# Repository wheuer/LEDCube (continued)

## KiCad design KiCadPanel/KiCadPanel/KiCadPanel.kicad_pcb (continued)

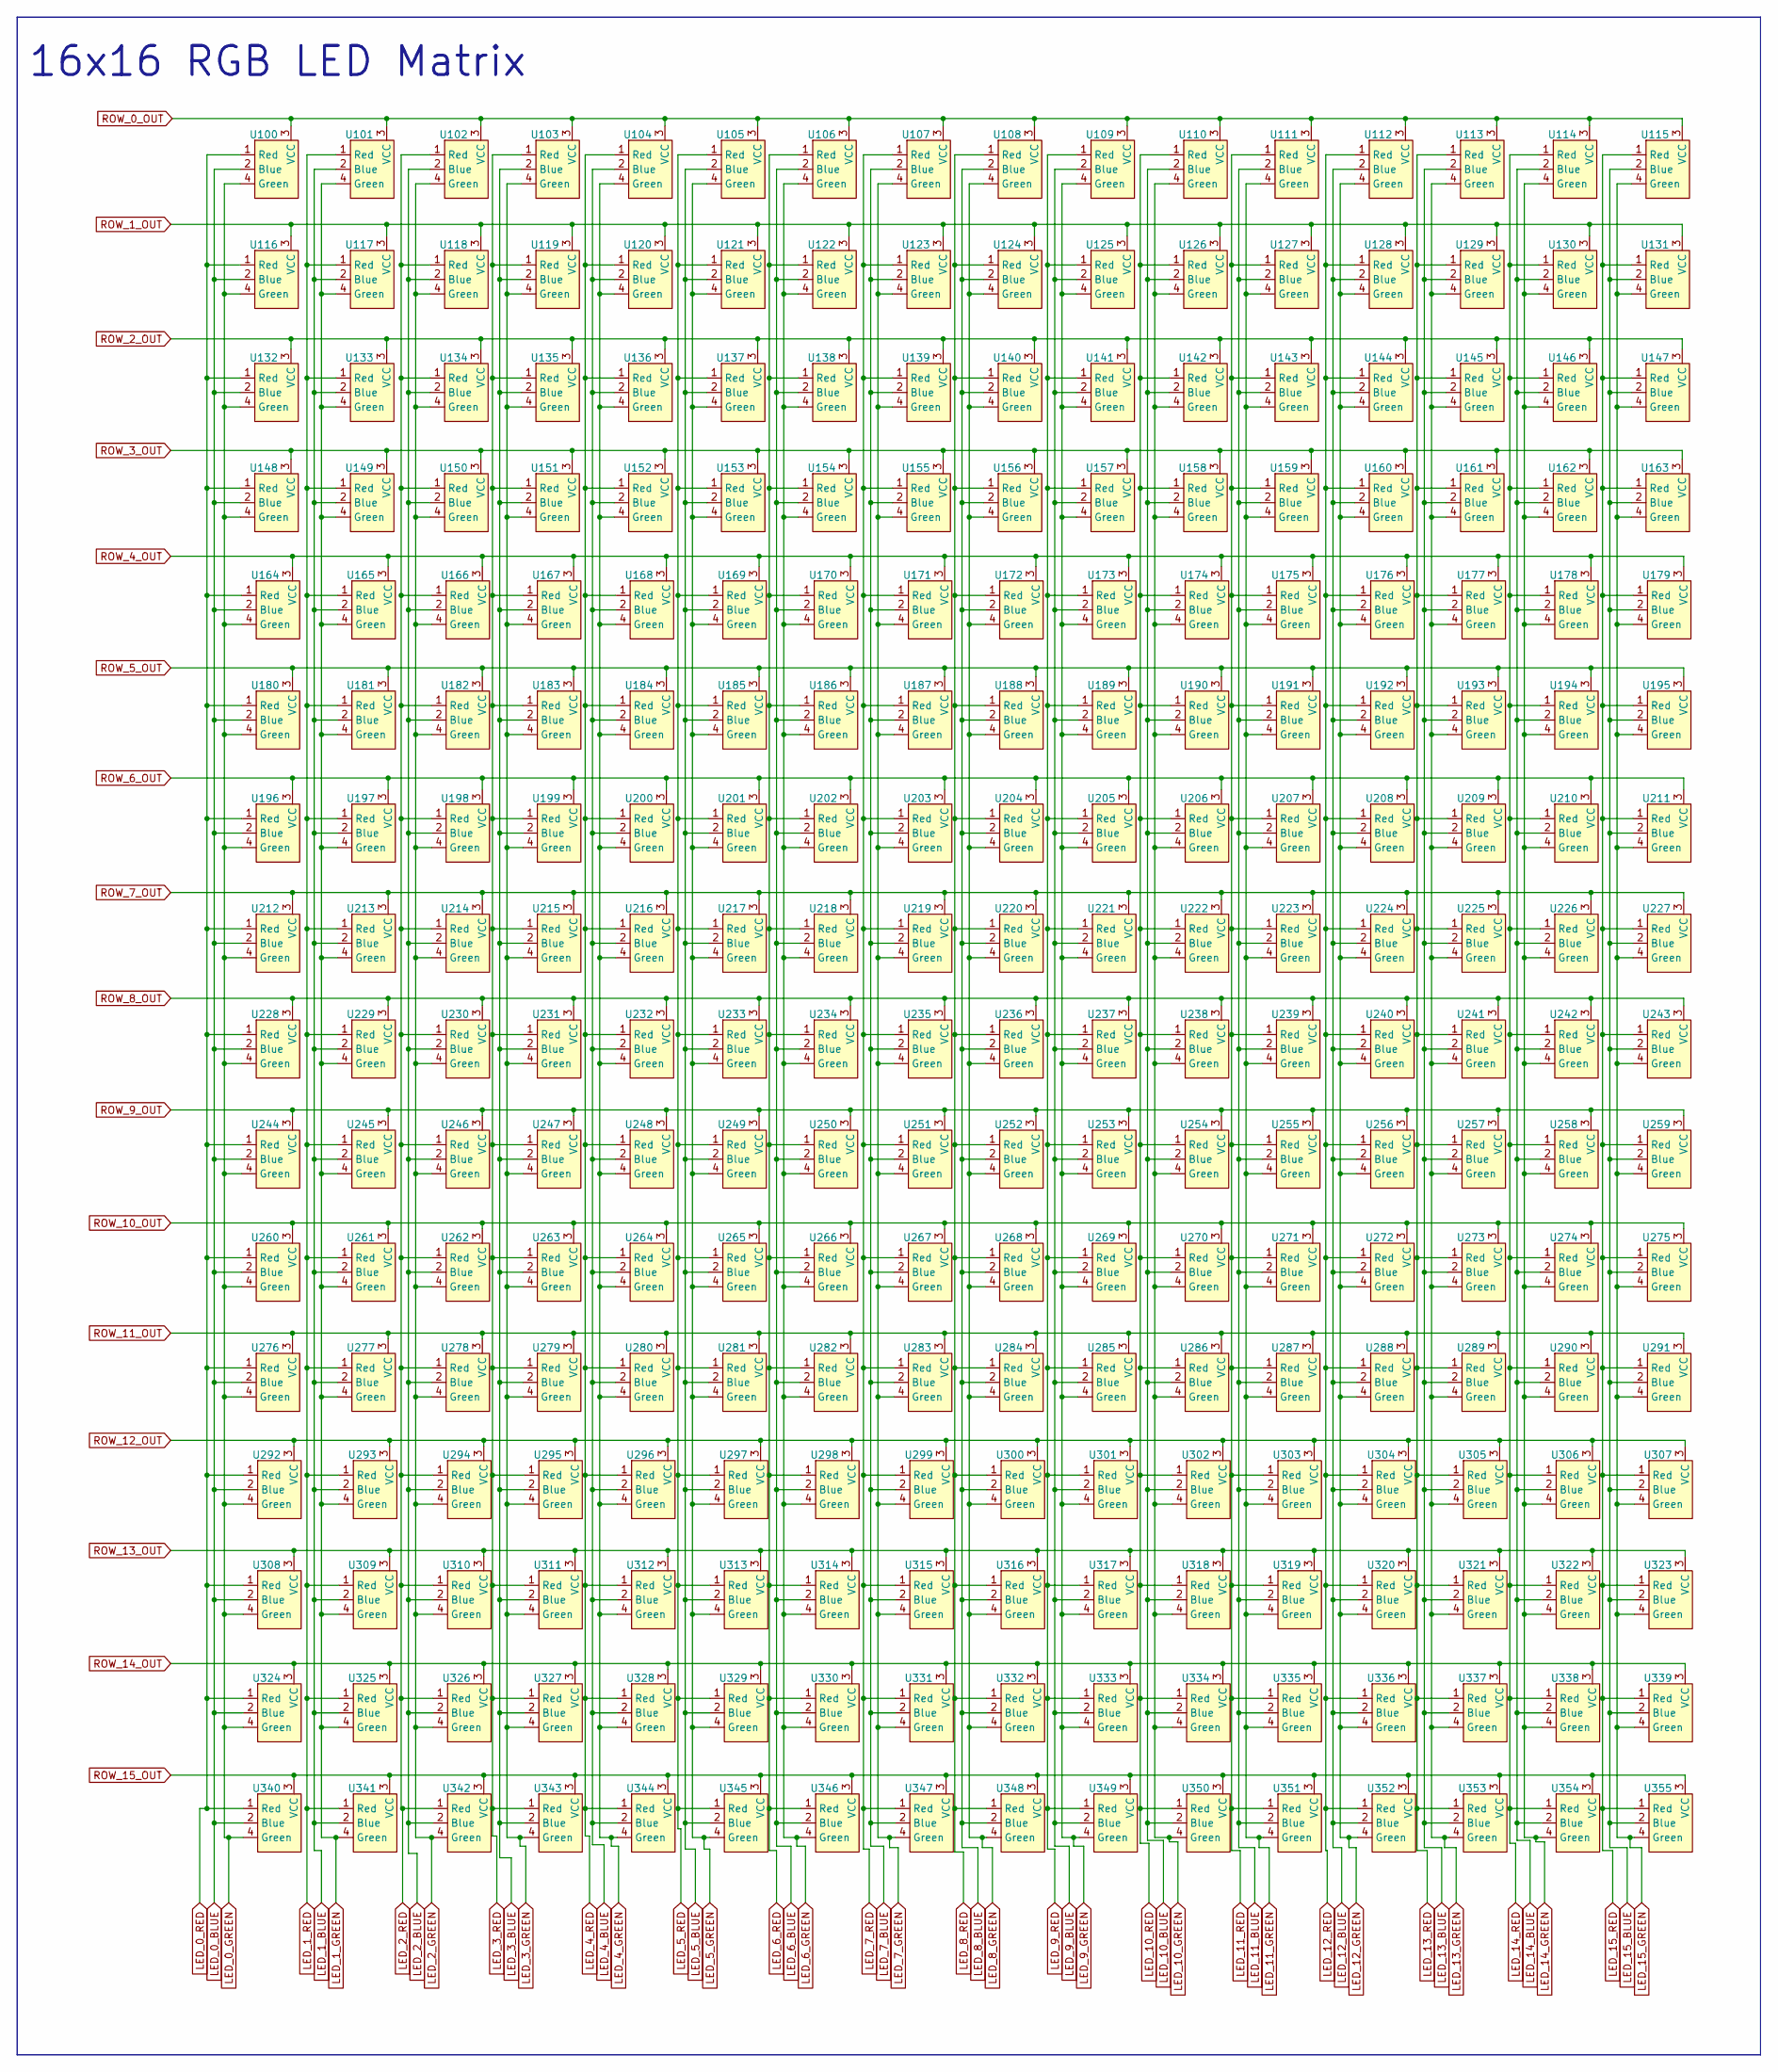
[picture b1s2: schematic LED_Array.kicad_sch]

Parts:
U100, U101, U102, U103, U104, U105, U106, U107, U108, U109, U110, U111, U112, U113, U114, U115, U116, U117, U118, U119, U120, U121, U122, U123, U124, U125, U126, U127, U128, U129, U130, U131, U132, U133, U134, U135, U136, U137, U138, U139, U140, U141, U142, U143, U144, U145, U146, U147, U148, U149, U150, U151, U152, U153, U154, U155, U156, U157, U158, U159, U160, U161, U162, U163, U164, U165, U166, U167, U168, U169, U170, U171, U172, U173, U174, U175, U176, U177, U178, U179, U180, U181, U182, U183, U184, U185, U186, U187, U188, U189, U190, U191, U192, U193, U194, U195, U196, U197, U198, U199, U200, U201, U202, U203, U204, U205, U206, U207, U208, U209, U210, U211, U212, U213, U214, U215, U216, U217, U218, U219, U220, U221, U222, U223, U224, U225, U226, U227, U228, U229, U230, U231, U232, U233, U234, U235, U236, U237, U238, U239, U240, U241, U242, U243, U244, U245, U246, U247, U248, U249, U250, U251, U252, U253, U254, U255, U256, U257, U258, U259, U260, U261, U262, U263, U264, U265, U266, U267, U268, U269, U270, U271, U272, U273, U274, U275, U276, U277, U278, U279, U280, U281, U282, U283, U284, U285, U286, U287, U288, U289, U290, U291, U292, U293, U294, U295, U296, U297, U298, U299, U300, U301, U302, U303, U304, U305, U306, U307, U308, U309, U310, U311, U312, U313, U314, U315, U316, U317, U318, U319, U320, U321, U322, U323, U324, U325, U326, U327, U328, U329, U330, U331, U332, U333, U334, U335, U336, U337, U338, U339, U340, U341, U342, U343, U344, U345, U346, U347, U348, U349, U350, U351, U352, U353, U354, U355: 2.1x2.1_LED

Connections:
LED_0_BLUE: U100.2 (Blue), U116.2 (Blue), U132.2 (Blue), U148.2 (Blue), U164.2 (Blue), U180.2 (Blue), U196.2 (Blue), U212.2 (Blue), U228.2 (Blue), U244.2 (Blue), U260.2 (Blue), U276.2 (Blue), U292.2 (Blue), U308.2 (Blue), U324.2 (Blue), U340.2 (Blue); also elsewhere on the board
LED_0_GREEN: U100.4 (Green), U116.4 (Green), U132.4 (Green), U148.4 (Green), U164.4 (Green), U180.4 (Green), U196.4 (Green), U212.4 (Green), U228.4 (Green), U244.4 (Green), U260.4 (Green), U276.4 (Green), U292.4 (Green), U308.4 (Green), U324.4 (Green), U340.4 (Green); also elsewhere on the board
LED_0_RED: U100.1 (Red), U116.1 (Red), U132.1 (Red), U148.1 (Red), U164.1 (Red), U180.1 (Red), U196.1 (Red), U212.1 (Red), U228.1 (Red), U244.1 (Red), U260.1 (Red), U276.1 (Red), U292.1 (Red), U308.1 (Red), U324.1 (Red), U340.1 (Red); also elsewhere on the board
LED_1_BLUE: U101.2 (Blue), U117.2 (Blue), U133.2 (Blue), U149.2 (Blue), U165.2 (Blue), U181.2 (Blue), U197.2 (Blue), U213.2 (Blue), U229.2 (Blue), U245.2 (Blue), U261.2 (Blue), U277.2 (Blue), U293.2 (Blue), U309.2 (Blue), U325.2 (Blue), U341.2 (Blue); also elsewhere on the board
LED_1_GREEN: U101.4 (Green), U117.4 (Green), U133.4 (Green), U149.4 (Green), U165.4 (Green), U181.4 (Green), U197.4 (Green), U213.4 (Green), U229.4 (Green), U245.4 (Green), U261.4 (Green), U277.4 (Green), U293.4 (Green), U309.4 (Green), U325.4 (Green), U341.4 (Green); also elsewhere on the board
LED_1_RED: U101.1 (Red), U117.1 (Red), U133.1 (Red), U149.1 (Red), U165.1 (Red), U181.1 (Red), U197.1 (Red), U213.1 (Red), U229.1 (Red), U245.1 (Red), U261.1 (Red), U277.1 (Red), U293.1 (Red), U309.1 (Red), U325.1 (Red), U341.1 (Red); also elsewhere on the board
LED_2_BLUE: U102.2 (Blue), U118.2 (Blue), U134.2 (Blue), U150.2 (Blue), U166.2 (Blue), U182.2 (Blue), U198.2 (Blue), U214.2 (Blue), U230.2 (Blue), U246.2 (Blue), U262.2 (Blue), U278.2 (Blue), U294.2 (Blue), U310.2 (Blue), U326.2 (Blue), U342.2 (Blue); also elsewhere on the board
LED_2_GREEN: U102.4 (Green), U118.4 (Green), U134.4 (Green), U150.4 (Green), U166.4 (Green), U182.4 (Green), U198.4 (Green), U214.4 (Green), U230.4 (Green), U246.4 (Green), U262.4 (Green), U278.4 (Green), U294.4 (Green), U310.4 (Green), U326.4 (Green), U342.4 (Green); also elsewhere on the board
LED_2_RED: U102.1 (Red), U118.1 (Red), U134.1 (Red), U150.1 (Red), U166.1 (Red), U182.1 (Red), U198.1 (Red), U214.1 (Red), U230.1 (Red), U246.1 (Red), U262.1 (Red), U278.1 (Red), U294.1 (Red), U310.1 (Red), U326.1 (Red), U342.1 (Red); also elsewhere on the board
LED_3_BLUE: U103.2 (Blue), U119.2 (Blue), U135.2 (Blue), U151.2 (Blue), U167.2 (Blue), U183.2 (Blue), U199.2 (Blue), U215.2 (Blue), U231.2 (Blue), U247.2 (Blue), U263.2 (Blue), U279.2 (Blue), U295.2 (Blue), U311.2 (Blue), U327.2 (Blue), U343.2 (Blue); also elsewhere on the board
LED_3_GREEN: U103.4 (Green), U119.4 (Green), U135.4 (Green), U151.4 (Green), U167.4 (Green), U183.4 (Green), U199.4 (Green), U215.4 (Green), U231.4 (Green), U247.4 (Green), U263.4 (Green), U279.4 (Green), U295.4 (Green), U311.4 (Green), U327.4 (Green), U343.4 (Green); also elsewhere on the board
LED_3_RED: U103.1 (Red), U119.1 (Red), U135.1 (Red), U151.1 (Red), U167.1 (Red), U183.1 (Red), U199.1 (Red), U215.1 (Red), U231.1 (Red), U247.1 (Red), U263.1 (Red), U279.1 (Red), U295.1 (Red), U311.1 (Red), U327.1 (Red), U343.1 (Red); also elsewhere on the board
LED_4_BLUE: U104.2 (Blue), U120.2 (Blue), U136.2 (Blue), U152.2 (Blue), U168.2 (Blue), U184.2 (Blue), U200.2 (Blue), U216.2 (Blue), U232.2 (Blue), U248.2 (Blue), U264.2 (Blue), U280.2 (Blue), U296.2 (Blue), U312.2 (Blue), U328.2 (Blue), U344.2 (Blue); also elsewhere on the board
LED_4_GREEN: U104.4 (Green), U120.4 (Green), U136.4 (Green), U152.4 (Green), U168.4 (Green), U184.4 (Green), U200.4 (Green), U216.4 (Green), U232.4 (Green), U248.4 (Green), U264.4 (Green), U280.4 (Green), U296.4 (Green), U312.4 (Green), U328.4 (Green), U344.4 (Green); also elsewhere on the board
LED_4_RED: U104.1 (Red), U120.1 (Red), U136.1 (Red), U152.1 (Red), U168.1 (Red), U184.1 (Red), U200.1 (Red), U216.1 (Red), U232.1 (Red), U248.1 (Red), U264.1 (Red), U280.1 (Red), U296.1 (Red), U312.1 (Red), U328.1 (Red), U344.1 (Red); also elsewhere on the board
LED_5_BLUE: U105.2 (Blue), U121.2 (Blue), U137.2 (Blue), U153.2 (Blue), U169.2 (Blue), U185.2 (Blue), U201.2 (Blue), U217.2 (Blue), U233.2 (Blue), U249.2 (Blue), U265.2 (Blue), U281.2 (Blue), U297.2 (Blue), U313.2 (Blue), U329.2 (Blue), U345.2 (Blue); also elsewhere on the board
LED_5_GREEN: U105.4 (Green), U121.4 (Green), U137.4 (Green), U153.4 (Green), U169.4 (Green), U185.4 (Green), U201.4 (Green), U217.4 (Green), U233.4 (Green), U249.4 (Green), U265.4 (Green), U281.4 (Green), U297.4 (Green), U313.4 (Green), U329.4 (Green), U345.4 (Green); also elsewhere on the board
LED_5_RED: U105.1 (Red), U121.1 (Red), U137.1 (Red), U153.1 (Red), U169.1 (Red), U185.1 (Red), U201.1 (Red), U217.1 (Red), U233.1 (Red), U249.1 (Red), U265.1 (Red), U281.1 (Red), U297.1 (Red), U313.1 (Red), U329.1 (Red), U345.1 (Red); also elsewhere on the board
LED_6_BLUE: U106.2 (Blue), U122.2 (Blue), U138.2 (Blue), U154.2 (Blue), U170.2 (Blue), U186.2 (Blue), U202.2 (Blue), U218.2 (Blue), U234.2 (Blue), U250.2 (Blue), U266.2 (Blue), U282.2 (Blue), U298.2 (Blue), U314.2 (Blue), U330.2 (Blue), U346.2 (Blue); also elsewhere on the board
LED_6_GREEN: U106.4 (Green), U122.4 (Green), U138.4 (Green), U154.4 (Green), U170.4 (Green), U186.4 (Green), U202.4 (Green), U218.4 (Green), U234.4 (Green), U250.4 (Green), U266.4 (Green), U282.4 (Green), U298.4 (Green), U314.4 (Green), U330.4 (Green), U346.4 (Green); also elsewhere on the board
LED_6_RED: U106.1 (Red), U122.1 (Red), U138.1 (Red), U154.1 (Red), U170.1 (Red), U186.1 (Red), U202.1 (Red), U218.1 (Red), U234.1 (Red), U250.1 (Red), U266.1 (Red), U282.1 (Red), U298.1 (Red), U314.1 (Red), U330.1 (Red), U346.1 (Red); also elsewhere on the board
LED_7_BLUE: U107.2 (Blue), U123.2 (Blue), U139.2 (Blue), U155.2 (Blue), U171.2 (Blue), U187.2 (Blue), U203.2 (Blue), U219.2 (Blue), U235.2 (Blue), U251.2 (Blue), U267.2 (Blue), U283.2 (Blue), U299.2 (Blue), U315.2 (Blue), U331.2 (Blue), U347.2 (Blue); also elsewhere on the board
LED_7_GREEN: U107.4 (Green), U123.4 (Green), U139.4 (Green), U155.4 (Green), U171.4 (Green), U187.4 (Green), U203.4 (Green), U219.4 (Green), U235.4 (Green), U251.4 (Green), U267.4 (Green), U283.4 (Green), U299.4 (Green), U315.4 (Green), U331.4 (Green), U347.4 (Green); also elsewhere on the board
LED_7_RED: U107.1 (Red), U123.1 (Red), U139.1 (Red), U155.1 (Red), U171.1 (Red), U187.1 (Red), U203.1 (Red), U219.1 (Red), U235.1 (Red), U251.1 (Red), U267.1 (Red), U283.1 (Red), U299.1 (Red), U315.1 (Red), U331.1 (Red), U347.1 (Red); also elsewhere on the board
LED_8_BLUE: U108.2 (Blue), U124.2 (Blue), U140.2 (Blue), U156.2 (Blue), U172.2 (Blue), U188.2 (Blue), U204.2 (Blue), U220.2 (Blue), U236.2 (Blue), U252.2 (Blue), U268.2 (Blue), U284.2 (Blue), U300.2 (Blue), U316.2 (Blue), U332.2 (Blue), U348.2 (Blue); also elsewhere on the board
LED_8_GREEN: U108.4 (Green), U124.4 (Green), U140.4 (Green), U156.4 (Green), U172.4 (Green), U188.4 (Green), U204.4 (Green), U220.4 (Green), U236.4 (Green), U252.4 (Green), U268.4 (Green), U284.4 (Green), U300.4 (Green), U316.4 (Green), U332.4 (Green), U348.4 (Green); also elsewhere on the board
LED_8_RED: U108.1 (Red), U124.1 (Red), U140.1 (Red), U156.1 (Red), U172.1 (Red), U188.1 (Red), U204.1 (Red), U220.1 (Red), U236.1 (Red), U252.1 (Red), U268.1 (Red), U284.1 (Red), U300.1 (Red), U316.1 (Red), U332.1 (Red), U348.1 (Red); also elsewhere on the board
LED_9_BLUE: U109.2 (Blue), U125.2 (Blue), U141.2 (Blue), U157.2 (Blue), U173.2 (Blue), U189.2 (Blue), U205.2 (Blue), U221.2 (Blue), U237.2 (Blue), U253.2 (Blue), U269.2 (Blue), U285.2 (Blue), U301.2 (Blue), U317.2 (Blue), U333.2 (Blue), U349.2 (Blue); also elsewhere on the board
LED_9_GREEN: U109.4 (Green), U125.4 (Green), U141.4 (Green), U157.4 (Green), U173.4 (Green), U189.4 (Green), U205.4 (Green), U221.4 (Green), U237.4 (Green), U253.4 (Green), U269.4 (Green), U285.4 (Green), U301.4 (Green), U317.4 (Green), U333.4 (Green), U349.4 (Green); also elsewhere on the board
LED_9_RED: U109.1 (Red), U125.1 (Red), U141.1 (Red), U157.1 (Red), U173.1 (Red), U189.1 (Red), U205.1 (Red), U221.1 (Red), U237.1 (Red), U253.1 (Red), U269.1 (Red), U285.1 (Red), U301.1 (Red), U317.1 (Red), U333.1 (Red), U349.1 (Red); also elsewhere on the board
LED_10_BLUE: U110.2 (Blue), U126.2 (Blue), U142.2 (Blue), U158.2 (Blue), U174.2 (Blue), U190.2 (Blue), U206.2 (Blue), U222.2 (Blue), U238.2 (Blue), U254.2 (Blue), U270.2 (Blue), U286.2 (Blue), U302.2 (Blue), U318.2 (Blue), U334.2 (Blue), U350.2 (Blue); also elsewhere on the board
LED_10_GREEN: U110.4 (Green), U126.4 (Green), U142.4 (Green), U158.4 (Green), U174.4 (Green), U190.4 (Green), U206.4 (Green), U222.4 (Green), U238.4 (Green), U254.4 (Green), U270.4 (Green), U286.4 (Green), U302.4 (Green), U318.4 (Green), U334.4 (Green), U350.4 (Green); also elsewhere on the board
LED_10_RED: U110.1 (Red), U126.1 (Red), U142.1 (Red), U158.1 (Red), U174.1 (Red), U190.1 (Red), U206.1 (Red), U222.1 (Red), U238.1 (Red), U254.1 (Red), U270.1 (Red), U286.1 (Red), U302.1 (Red), U318.1 (Red), U334.1 (Red), U350.1 (Red); also elsewhere on the board
LED_11_BLUE: U111.2 (Blue), U127.2 (Blue), U143.2 (Blue), U159.2 (Blue), U175.2 (Blue), U191.2 (Blue), U207.2 (Blue), U223.2 (Blue), U239.2 (Blue), U255.2 (Blue), U271.2 (Blue), U287.2 (Blue), U303.2 (Blue), U319.2 (Blue), U335.2 (Blue), U351.2 (Blue); also elsewhere on the board
LED_11_GREEN: U111.4 (Green), U127.4 (Green), U143.4 (Green), U159.4 (Green), U175.4 (Green), U191.4 (Green), U207.4 (Green), U223.4 (Green), U239.4 (Green), U255.4 (Green), U271.4 (Green), U287.4 (Green), U303.4 (Green), U319.4 (Green), U335.4 (Green), U351.4 (Green); also elsewhere on the board
LED_11_RED: U111.1 (Red), U127.1 (Red), U143.1 (Red), U159.1 (Red), U175.1 (Red), U191.1 (Red), U207.1 (Red), U223.1 (Red), U239.1 (Red), U255.1 (Red), U271.1 (Red), U287.1 (Red), U303.1 (Red), U319.1 (Red), U335.1 (Red), U351.1 (Red); also elsewhere on the board
LED_12_BLUE: U112.2 (Blue), U128.2 (Blue), U144.2 (Blue), U160.2 (Blue), U176.2 (Blue), U192.2 (Blue), U208.2 (Blue), U224.2 (Blue), U240.2 (Blue), U256.2 (Blue), U272.2 (Blue), U288.2 (Blue), U304.2 (Blue), U320.2 (Blue), U336.2 (Blue), U352.2 (Blue); also elsewhere on the board
LED_12_GREEN: U112.4 (Green), U128.4 (Green), U144.4 (Green), U160.4 (Green), U176.4 (Green), U192.4 (Green), U208.4 (Green), U224.4 (Green), U240.4 (Green), U256.4 (Green), U272.4 (Green), U288.4 (Green), U304.4 (Green), U320.4 (Green), U336.4 (Green), U352.4 (Green); also elsewhere on the board
LED_12_RED: U112.1 (Red), U128.1 (Red), U144.1 (Red), U160.1 (Red), U176.1 (Red), U192.1 (Red), U208.1 (Red), U224.1 (Red), U240.1 (Red), U256.1 (Red), U272.1 (Red), U288.1 (Red), U304.1 (Red), U320.1 (Red), U336.1 (Red), U352.1 (Red); also elsewhere on the board
LED_13_BLUE: U113.2 (Blue), U129.2 (Blue), U145.2 (Blue), U161.2 (Blue), U177.2 (Blue), U193.2 (Blue), U209.2 (Blue), U225.2 (Blue), U241.2 (Blue), U257.2 (Blue), U273.2 (Blue), U289.2 (Blue), U305.2 (Blue), U321.2 (Blue), U337.2 (Blue), U353.2 (Blue); also elsewhere on the board
LED_13_GREEN: U113.4 (Green), U129.4 (Green), U145.4 (Green), U161.4 (Green), U177.4 (Green), U193.4 (Green), U209.4 (Green), U225.4 (Green), U241.4 (Green), U257.4 (Green), U273.4 (Green), U289.4 (Green), U305.4 (Green), U321.4 (Green), U337.4 (Green), U353.4 (Green); also elsewhere on the board
LED_13_RED: U113.1 (Red), U129.1 (Red), U145.1 (Red), U161.1 (Red), U177.1 (Red), U193.1 (Red), U209.1 (Red), U225.1 (Red), U241.1 (Red), U257.1 (Red), U273.1 (Red), U289.1 (Red), U305.1 (Red), U321.1 (Red), U337.1 (Red), U353.1 (Red); also elsewhere on the board
LED_14_BLUE: U114.2 (Blue), U130.2 (Blue), U146.2 (Blue), U162.2 (Blue), U178.2 (Blue), U194.2 (Blue), U210.2 (Blue), U226.2 (Blue), U242.2 (Blue), U258.2 (Blue), U274.2 (Blue), U290.2 (Blue), U306.2 (Blue), U322.2 (Blue), U338.2 (Blue), U354.2 (Blue); also elsewhere on the board
LED_14_GREEN: U114.4 (Green), U130.4 (Green), U146.4 (Green), U162.4 (Green), U178.4 (Green), U194.4 (Green), U210.4 (Green), U226.4 (Green), U242.4 (Green), U258.4 (Green), U274.4 (Green), U290.4 (Green), U306.4 (Green), U322.4 (Green), U338.4 (Green), U354.4 (Green); also elsewhere on the board
LED_14_RED: U114.1 (Red), U130.1 (Red), U146.1 (Red), U162.1 (Red), U178.1 (Red), U194.1 (Red), U210.1 (Red), U226.1 (Red), U242.1 (Red), U258.1 (Red), U274.1 (Red), U290.1 (Red), U306.1 (Red), U322.1 (Red), U338.1 (Red), U354.1 (Red); also elsewhere on the board
LED_15_BLUE: U115.2 (Blue), U131.2 (Blue), U147.2 (Blue), U163.2 (Blue), U179.2 (Blue), U195.2 (Blue), U211.2 (Blue), U227.2 (Blue), U243.2 (Blue), U259.2 (Blue), U275.2 (Blue), U291.2 (Blue), U307.2 (Blue), U323.2 (Blue), U339.2 (Blue), U355.2 (Blue); also elsewhere on the board
LED_15_GREEN: U115.4 (Green), U131.4 (Green), U147.4 (Green), U163.4 (Green), U179.4 (Green), U195.4 (Green), U211.4 (Green), U227.4 (Green), U243.4 (Green), U259.4 (Green), U275.4 (Green), U291.4 (Green), U307.4 (Green), U323.4 (Green), U339.4 (Green), U355.4 (Green); also elsewhere on the board
LED_15_RED: U115.1 (Red), U131.1 (Red), U147.1 (Red), U163.1 (Red), U179.1 (Red), U195.1 (Red), U211.1 (Red), U227.1 (Red), U243.1 (Red), U259.1 (Red), U275.1 (Red), U291.1 (Red), U307.1 (Red), U323.1 (Red), U339.1 (Red), U355.1 (Red); also elsewhere on the board
ROW_0_OUT: U100.3 (VCC), U101.3 (VCC), U102.3 (VCC), U103.3 (VCC), U104.3 (VCC), U105.3 (VCC), U106.3 (VCC), U107.3 (VCC), U108.3 (VCC), U109.3 (VCC), U110.3 (VCC), U111.3 (VCC), U112.3 (VCC), U113.3 (VCC), U114.3 (VCC), U115.3 (VCC); also elsewhere on the board
ROW_1_OUT: U116.3 (VCC), U117.3 (VCC), U118.3 (VCC), U119.3 (VCC), U120.3 (VCC), U121.3 (VCC), U122.3 (VCC), U123.3 (VCC), U124.3 (VCC), U125.3 (VCC), U126.3 (VCC), U127.3 (VCC), U128.3 (VCC), U129.3 (VCC), U130.3 (VCC), U131.3 (VCC); also elsewhere on the board
ROW_2_OUT: U132.3 (VCC), U133.3 (VCC), U134.3 (VCC), U135.3 (VCC), U136.3 (VCC), U137.3 (VCC), U138.3 (VCC), U139.3 (VCC), U140.3 (VCC), U141.3 (VCC), U142.3 (VCC), U143.3 (VCC), U144.3 (VCC), U145.3 (VCC), U146.3 (VCC), U147.3 (VCC); also elsewhere on the board
ROW_3_OUT: U148.3 (VCC), U149.3 (VCC), U150.3 (VCC), U151.3 (VCC), U152.3 (VCC), U153.3 (VCC), U154.3 (VCC), U155.3 (VCC), U156.3 (VCC), U157.3 (VCC), U158.3 (VCC), U159.3 (VCC), U160.3 (VCC), U161.3 (VCC), U162.3 (VCC), U163.3 (VCC); also elsewhere on the board
ROW_4_OUT: U164.3 (VCC), U165.3 (VCC), U166.3 (VCC), U167.3 (VCC), U168.3 (VCC), U169.3 (VCC), U170.3 (VCC), U171.3 (VCC), U172.3 (VCC), U173.3 (VCC), U174.3 (VCC), U175.3 (VCC), U176.3 (VCC), U177.3 (VCC), U178.3 (VCC), U179.3 (VCC); also elsewhere on the board
ROW_5_OUT: U180.3 (VCC), U181.3 (VCC), U182.3 (VCC), U183.3 (VCC), U184.3 (VCC), U185.3 (VCC), U186.3 (VCC), U187.3 (VCC), U188.3 (VCC), U189.3 (VCC), U190.3 (VCC), U191.3 (VCC), U192.3 (VCC), U193.3 (VCC), U194.3 (VCC), U195.3 (VCC); also elsewhere on the board
ROW_6_OUT: U196.3 (VCC), U197.3 (VCC), U198.3 (VCC), U199.3 (VCC), U200.3 (VCC), U201.3 (VCC), U202.3 (VCC), U203.3 (VCC), U204.3 (VCC), U205.3 (VCC), U206.3 (VCC), U207.3 (VCC), U208.3 (VCC), U209.3 (VCC), U210.3 (VCC), U211.3 (VCC); also elsewhere on the board
ROW_7_OUT: U212.3 (VCC), U213.3 (VCC), U214.3 (VCC), U215.3 (VCC), U216.3 (VCC), U217.3 (VCC), U218.3 (VCC), U219.3 (VCC), U220.3 (VCC), U221.3 (VCC), U222.3 (VCC), U223.3 (VCC), U224.3 (VCC), U225.3 (VCC), U226.3 (VCC), U227.3 (VCC); also elsewhere on the board
ROW_8_OUT: U228.3 (VCC), U229.3 (VCC), U230.3 (VCC), U231.3 (VCC), U232.3 (VCC), U233.3 (VCC), U234.3 (VCC), U235.3 (VCC), U236.3 (VCC), U237.3 (VCC), U238.3 (VCC), U239.3 (VCC), U240.3 (VCC), U241.3 (VCC), U242.3 (VCC), U243.3 (VCC); also elsewhere on the board
ROW_9_OUT: U244.3 (VCC), U245.3 (VCC), U246.3 (VCC), U247.3 (VCC), U248.3 (VCC), U249.3 (VCC), U250.3 (VCC), U251.3 (VCC), U252.3 (VCC), U253.3 (VCC), U254.3 (VCC), U255.3 (VCC), U256.3 (VCC), U257.3 (VCC), U258.3 (VCC), U259.3 (VCC); also elsewhere on the board
ROW_10_OUT: U260.3 (VCC), U261.3 (VCC), U262.3 (VCC), U263.3 (VCC), U264.3 (VCC), U265.3 (VCC), U266.3 (VCC), U267.3 (VCC), U268.3 (VCC), U269.3 (VCC), U270.3 (VCC), U271.3 (VCC), U272.3 (VCC), U273.3 (VCC), U274.3 (VCC), U275.3 (VCC); also elsewhere on the board
ROW_11_OUT: U276.3 (VCC), U277.3 (VCC), U278.3 (VCC), U279.3 (VCC), U280.3 (VCC), U281.3 (VCC), U282.3 (VCC), U283.3 (VCC), U284.3 (VCC), U285.3 (VCC), U286.3 (VCC), U287.3 (VCC), U288.3 (VCC), U289.3 (VCC), U290.3 (VCC), U291.3 (VCC); also elsewhere on the board
ROW_12_OUT: U292.3 (VCC), U293.3 (VCC), U294.3 (VCC), U295.3 (VCC), U296.3 (VCC), U297.3 (VCC), U298.3 (VCC), U299.3 (VCC), U300.3 (VCC), U301.3 (VCC), U302.3 (VCC), U303.3 (VCC), U304.3 (VCC), U305.3 (VCC), U306.3 (VCC), U307.3 (VCC); also elsewhere on the board
ROW_13_OUT: U308.3 (VCC), U309.3 (VCC), U310.3 (VCC), U311.3 (VCC), U312.3 (VCC), U313.3 (VCC), U314.3 (VCC), U315.3 (VCC), U316.3 (VCC), U317.3 (VCC), U318.3 (VCC), U319.3 (VCC), U320.3 (VCC), U321.3 (VCC), U322.3 (VCC), U323.3 (VCC); also elsewhere on the board
ROW_14_OUT: U324.3 (VCC), U325.3 (VCC), U326.3 (VCC), U327.3 (VCC), U328.3 (VCC), U329.3 (VCC), U330.3 (VCC), U331.3 (VCC), U332.3 (VCC), U333.3 (VCC), U334.3 (VCC), U335.3 (VCC), U336.3 (VCC), U337.3 (VCC), U338.3 (VCC), U339.3 (VCC); also elsewhere on the board
ROW_15_OUT: U340.3 (VCC), U341.3 (VCC), U342.3 (VCC), U343.3 (VCC), U344.3 (VCC), U345.3 (VCC), U346.3 (VCC), U347.3 (VCC), U348.3 (VCC), U349.3 (VCC), U350.3 (VCC), U351.3 (VCC), U352.3 (VCC), U353.3 (VCC), U354.3 (VCC), U355.3 (VCC); also elsewhere on the board

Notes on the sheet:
16x16 RGB LED Matrix

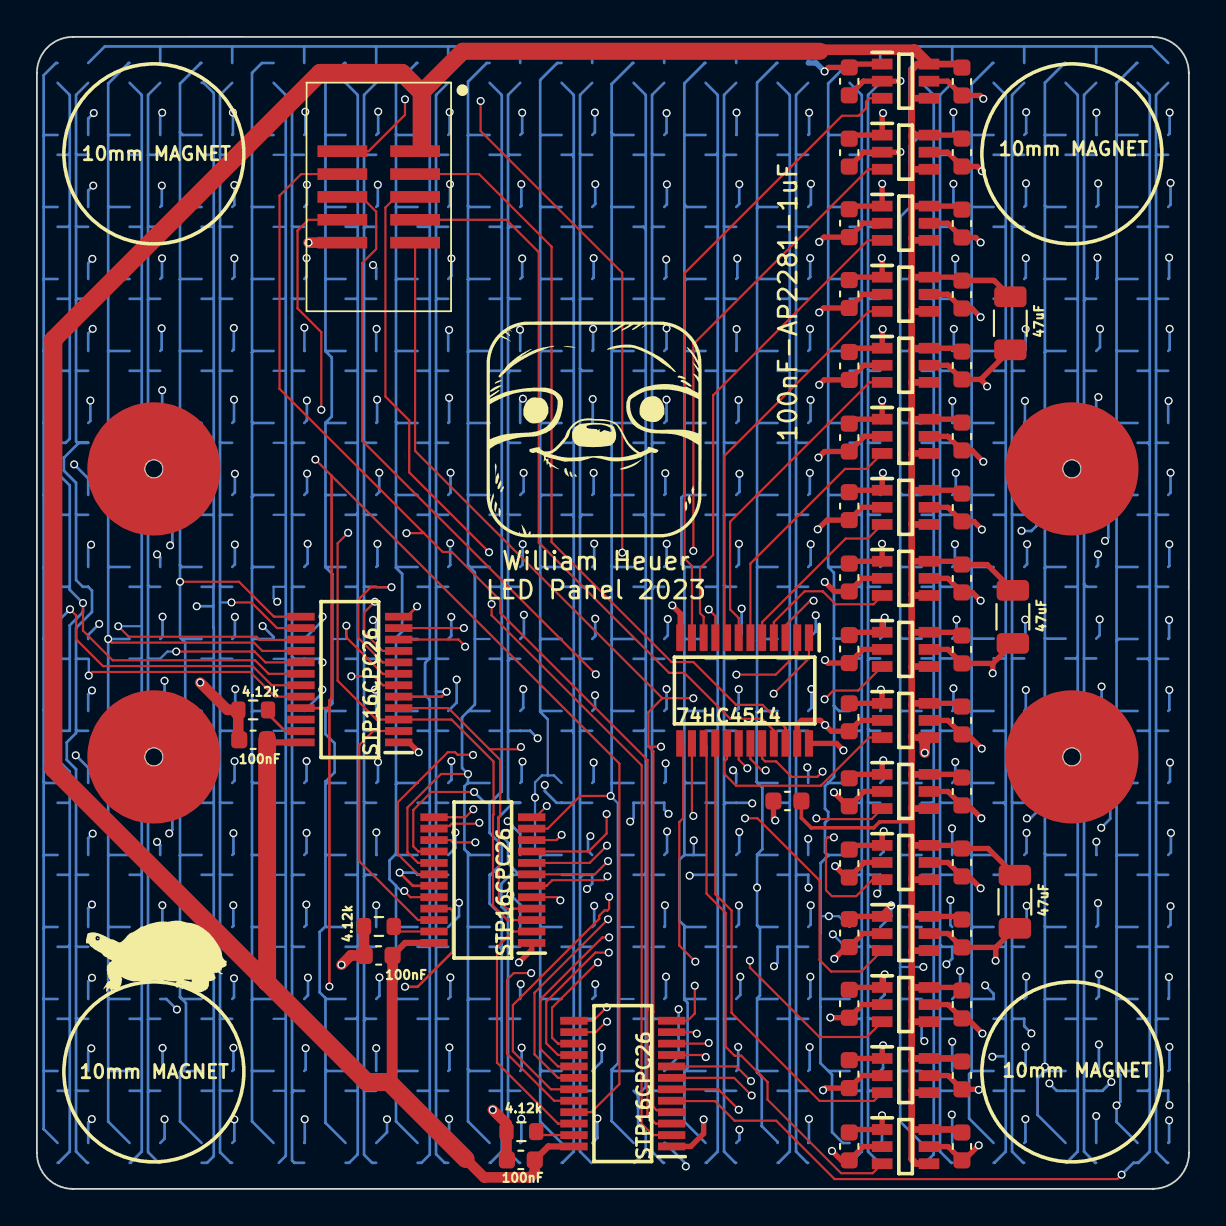
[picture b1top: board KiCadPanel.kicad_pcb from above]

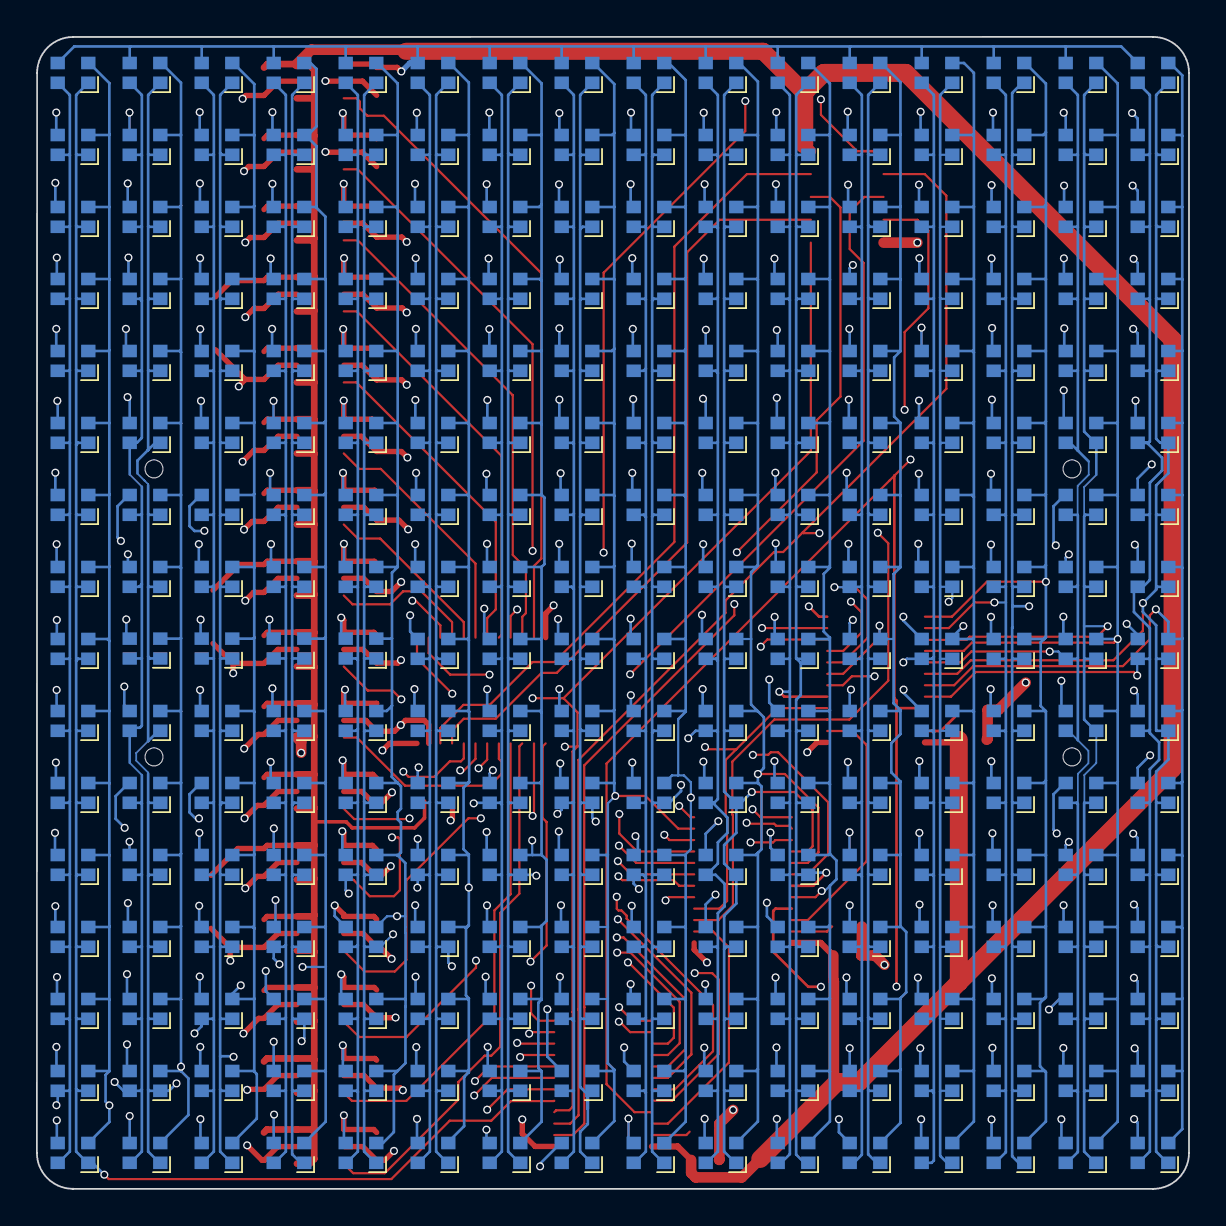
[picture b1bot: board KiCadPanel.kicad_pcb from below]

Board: 4 copper layers, 64.0 x 64.0 mm, 323 parts (256 on the bottom side), 95 nets.
